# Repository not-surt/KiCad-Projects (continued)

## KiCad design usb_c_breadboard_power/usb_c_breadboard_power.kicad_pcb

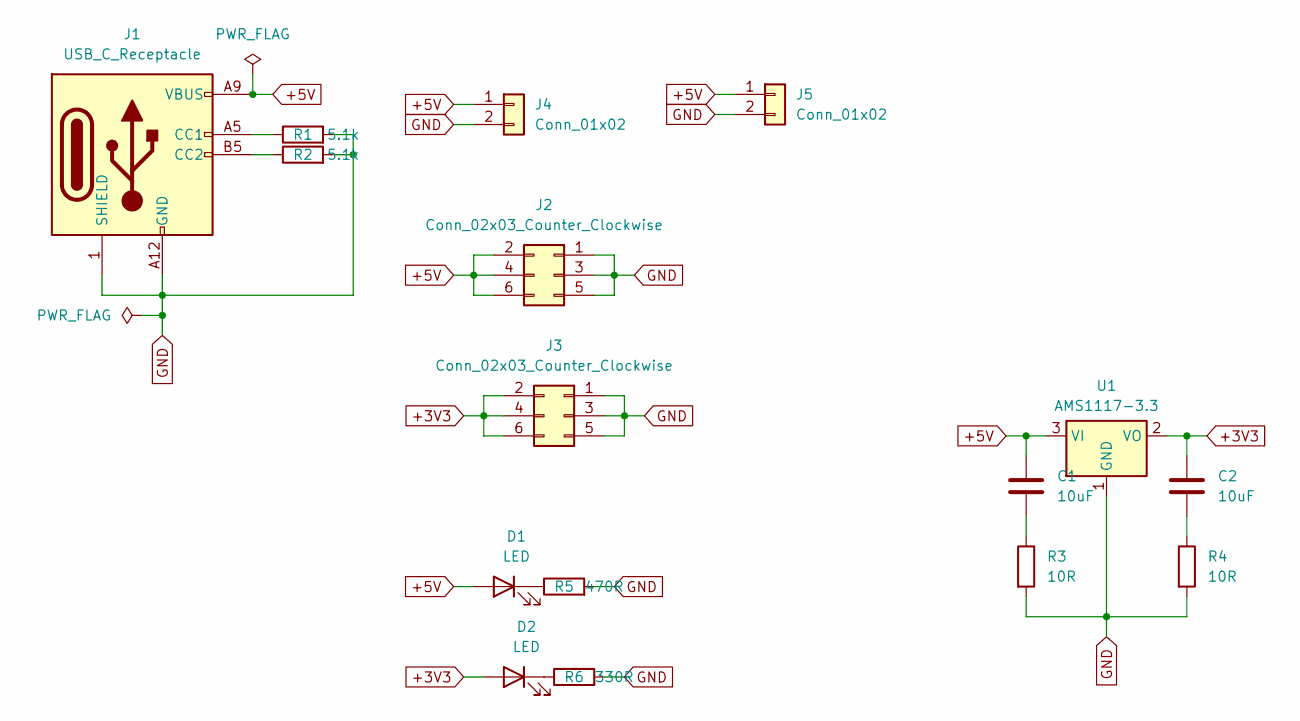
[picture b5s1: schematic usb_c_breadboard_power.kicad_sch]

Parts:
C1, C2: 10uF; C_0805_2012Metric_Pad1.18x1.45mm_HandSolder
D1, D2: LED; LED_0805_2012Metric_Pad1.15x1.40mm_HandSolder
J1: USB_C_Receptacle; TYPE-C-31-M-17_handsolder
J2, J3: Conn_02x03_Counter_Clockwise; PinHeader_2x03_P2.54mm_Vertical
J4, J5: Conn_01x02; PinHeader_1x02_P2.54mm_Vertical
R1, R2: 5.1k; R_0805_2012Metric_Pad1.20x1.40mm_HandSolder
R3, R4: 10R; R_0805_2012Metric_Pad1.20x1.40mm_HandSolder
R5: 470R; R_0805_2012Metric_Pad1.20x1.40mm_HandSolder
R6: 330R; R_0805_2012Metric_Pad1.20x1.40mm_HandSolder
U1: AMS1117-3.3; SOT-223-3_TabPin2

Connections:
+3V3: C2.1, D2.2 (A), J3.2, J3.4, J3.6, U1.2 (VO)
+5V: C1.1, D1.2 (A), J1.A9 (VBUS), J1.B9 (VBUS), J2.2, J2.4, J2.6, J4.1, J5.1, U1.3 (VI)
GND: J1.1 (SHIELD), J1.A12 (GND), J1.B12 (GND), J2.1, J2.3, J2.5, J3.1, J3.3, J3.5, J4.2, J5.2, R1.2, R2.2, R3.2, R4.2, R5.2, R6.2, U1.1 (GND)
unnamed: C1.2, R3.1
unnamed: C2.2, R4.1
unnamed: D1.1 (K), R5.1
unnamed: D2.1 (K), R6.1
unnamed: J1.A5 (CC1), R1.1
unnamed: J1.B5 (CC2), R2.1

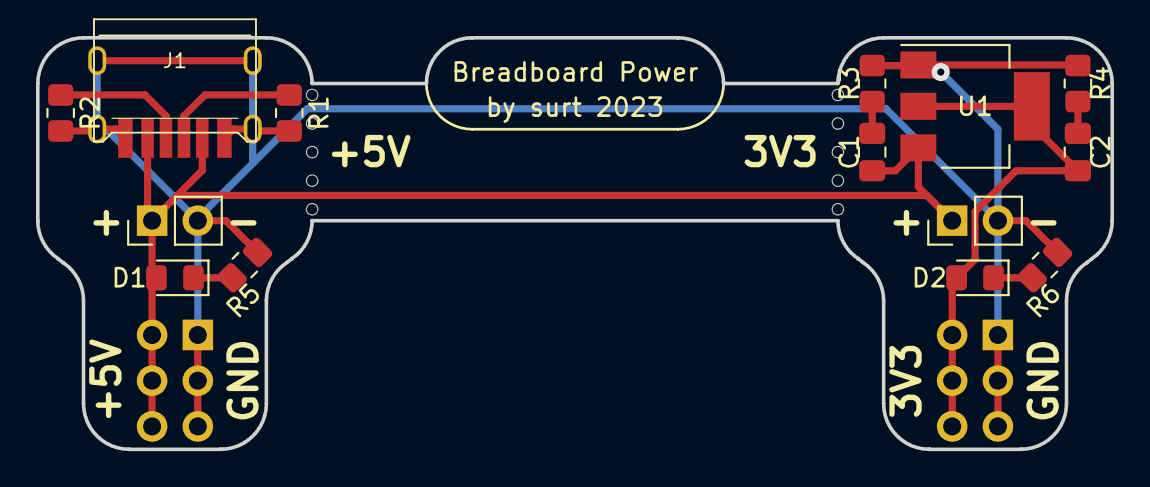
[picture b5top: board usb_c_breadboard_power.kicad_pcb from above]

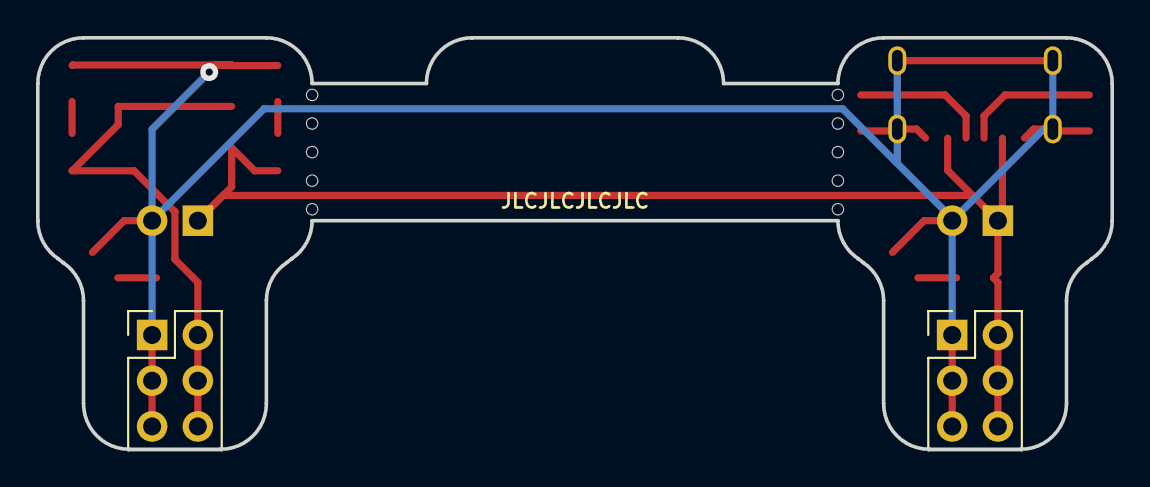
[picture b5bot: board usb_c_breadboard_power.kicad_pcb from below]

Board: 2 copper layers, 59.7 x 22.9 mm, 16 parts (2 on the bottom side), 9 nets.
